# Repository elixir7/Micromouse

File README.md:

# Jerry the micromouse

# Who is Jerry?
Jerry is a tiny (10x8 cm) high performance robot for the robotics competition Micromouse. 

The competition goal is to search a 16x16 grid maze which is 3x3 m^2 as fast as possible and find the path to the center.

Then you run from start to goal with your calculated route. 

To get the competition you take 1/30 of the search time and the run time.

World class mice are extremly fast, [have a look.](https://www.youtube.com/watch?v=NqdZ9wbXt8k&t=150s)

# Structure & Development
Hardware:
-   <b>3D_Models</b>,       pcb components, motor mount, rims etc.
-   <b>drawings</b>,        .dxf files
-   <b>pcb</b>,             EAGLE CAD files
-   <b>gerbers.zip</b>,     manufacturing files for pcb (Jerry was made by [JLC PCB](https://www.jlcpcb.com)
-   <b>jlcpcb.cam</b>,      CAM job for creating gerber files to JLC standard in EAGLE.

Software:
-   <b>Eagle</b>,           E-CAD for making PCB
-   <b>Fusion 360</b>,      M-CAD for making board outline, motor mounts, rims, etc.
-   <b>Keil uVision 5</b>,  IDE for C programming/debugging on Microcontrollers

Images:
-   Renders of jerry

## Software
- MCU configuration (pins, clock, etc) using STM32CubeMX
- Keil uVision 5 project
    - Low level drivers (motors, sensors, screen)
    - High level maze solving algoritm

## Contributors
-   Isak Åslund, aslundisak@gmail.com

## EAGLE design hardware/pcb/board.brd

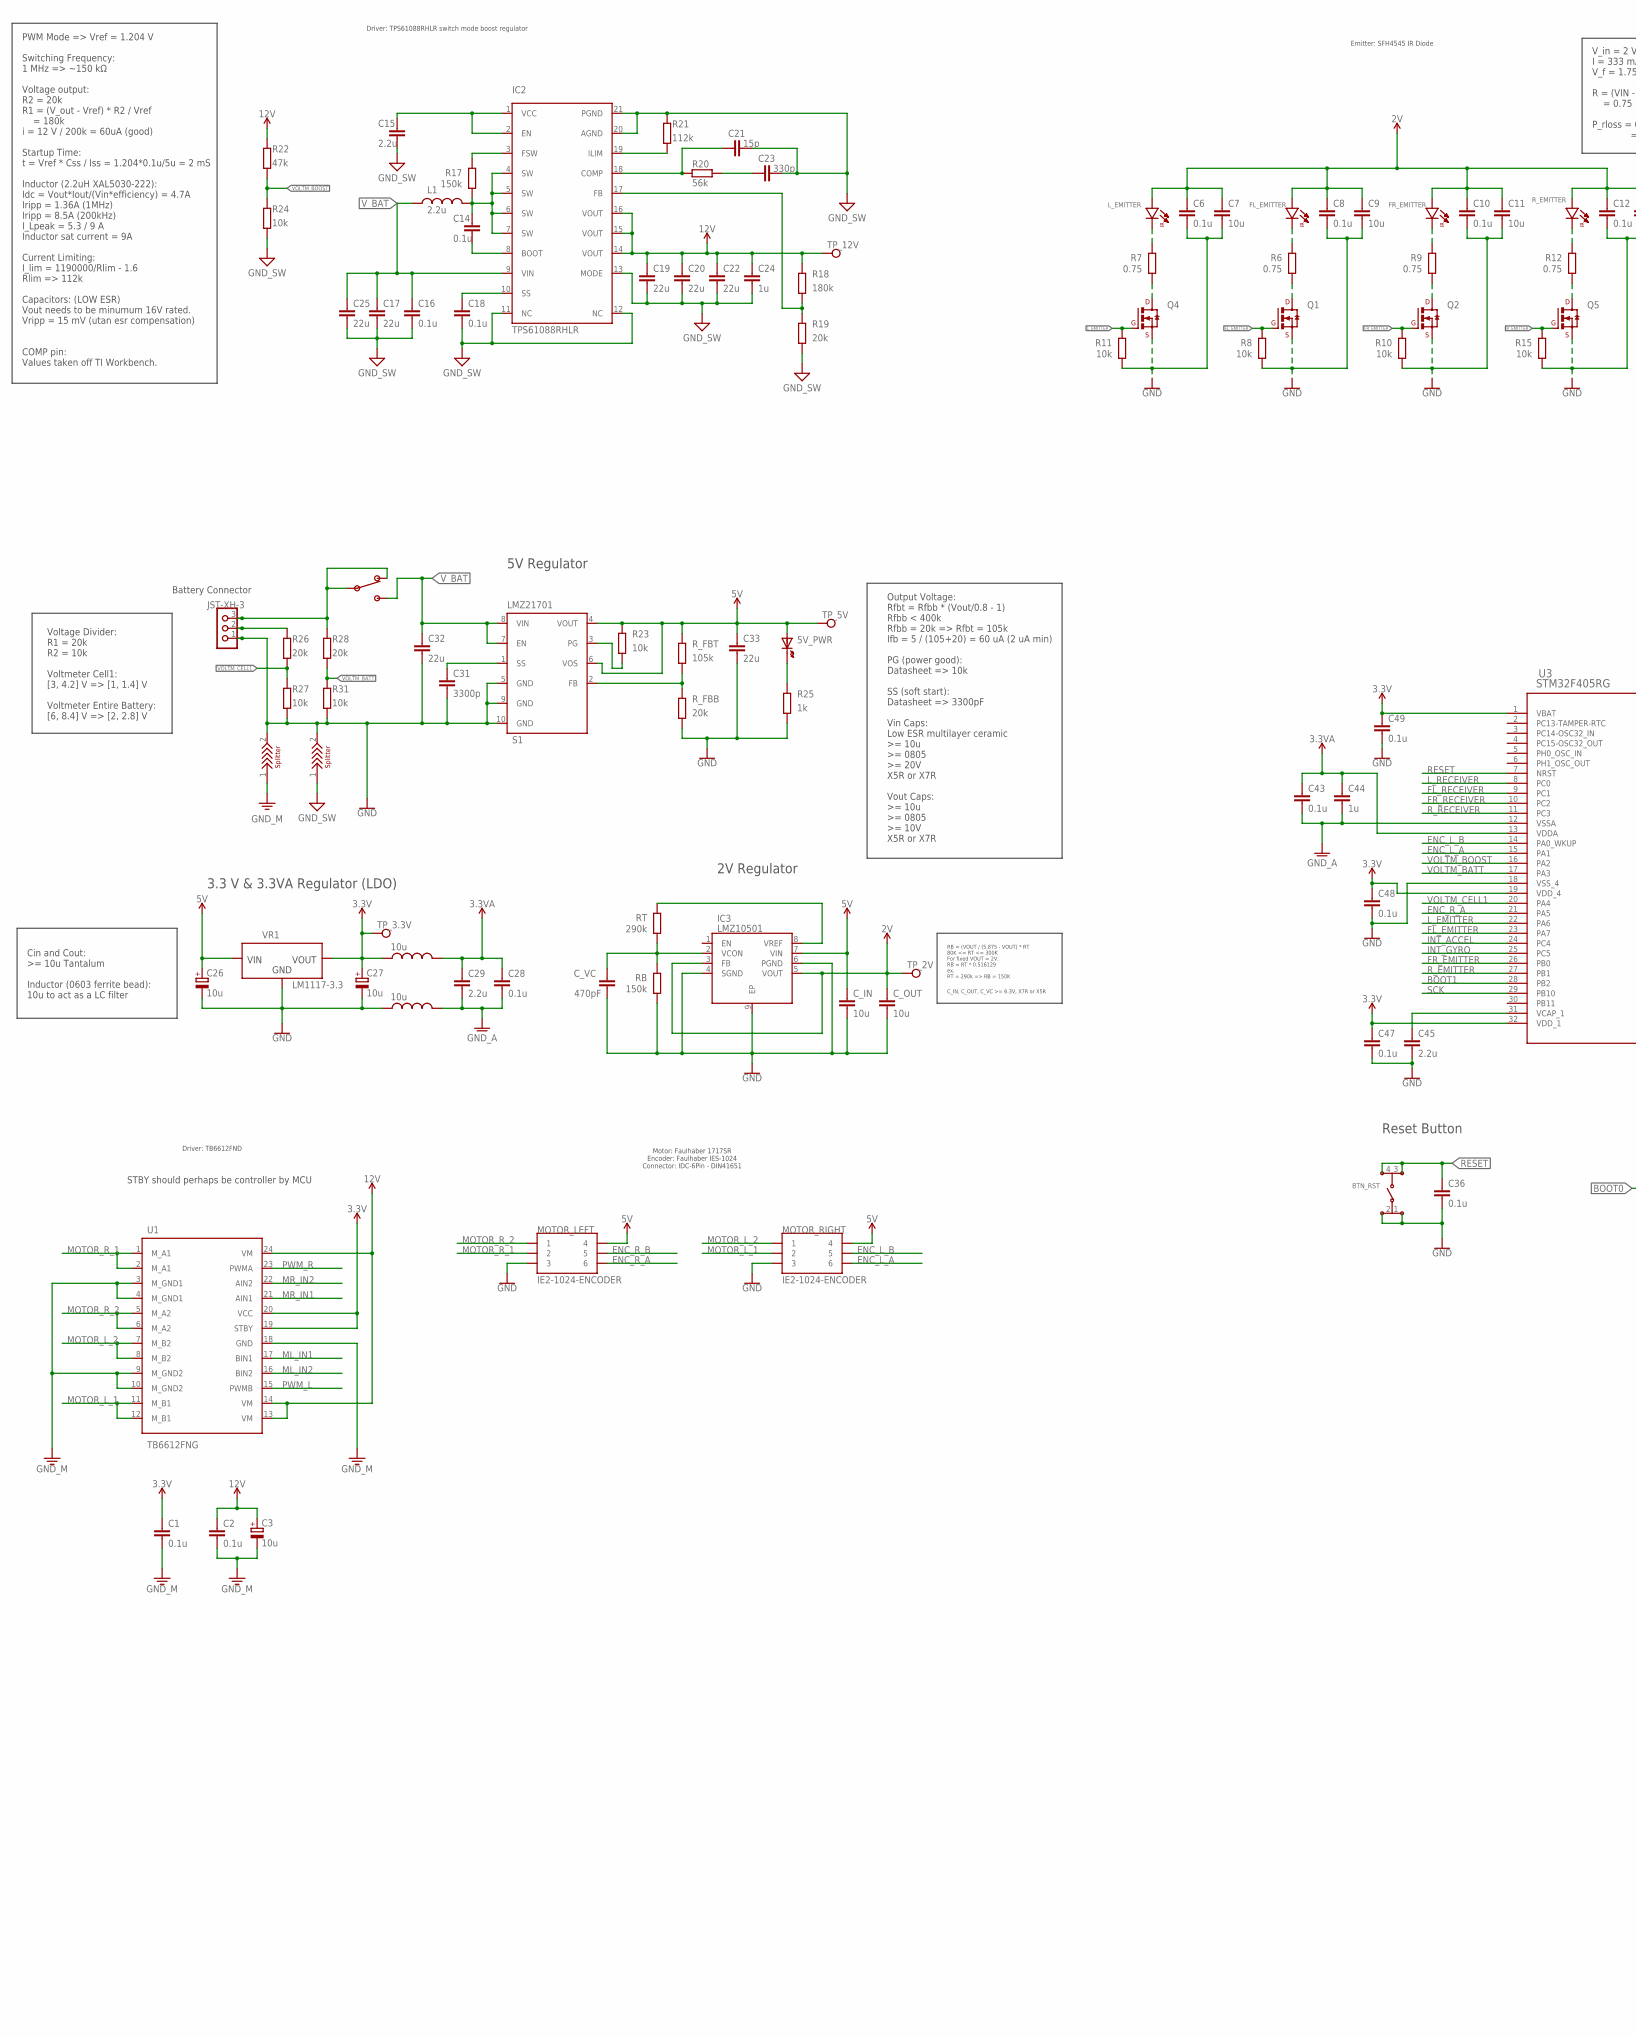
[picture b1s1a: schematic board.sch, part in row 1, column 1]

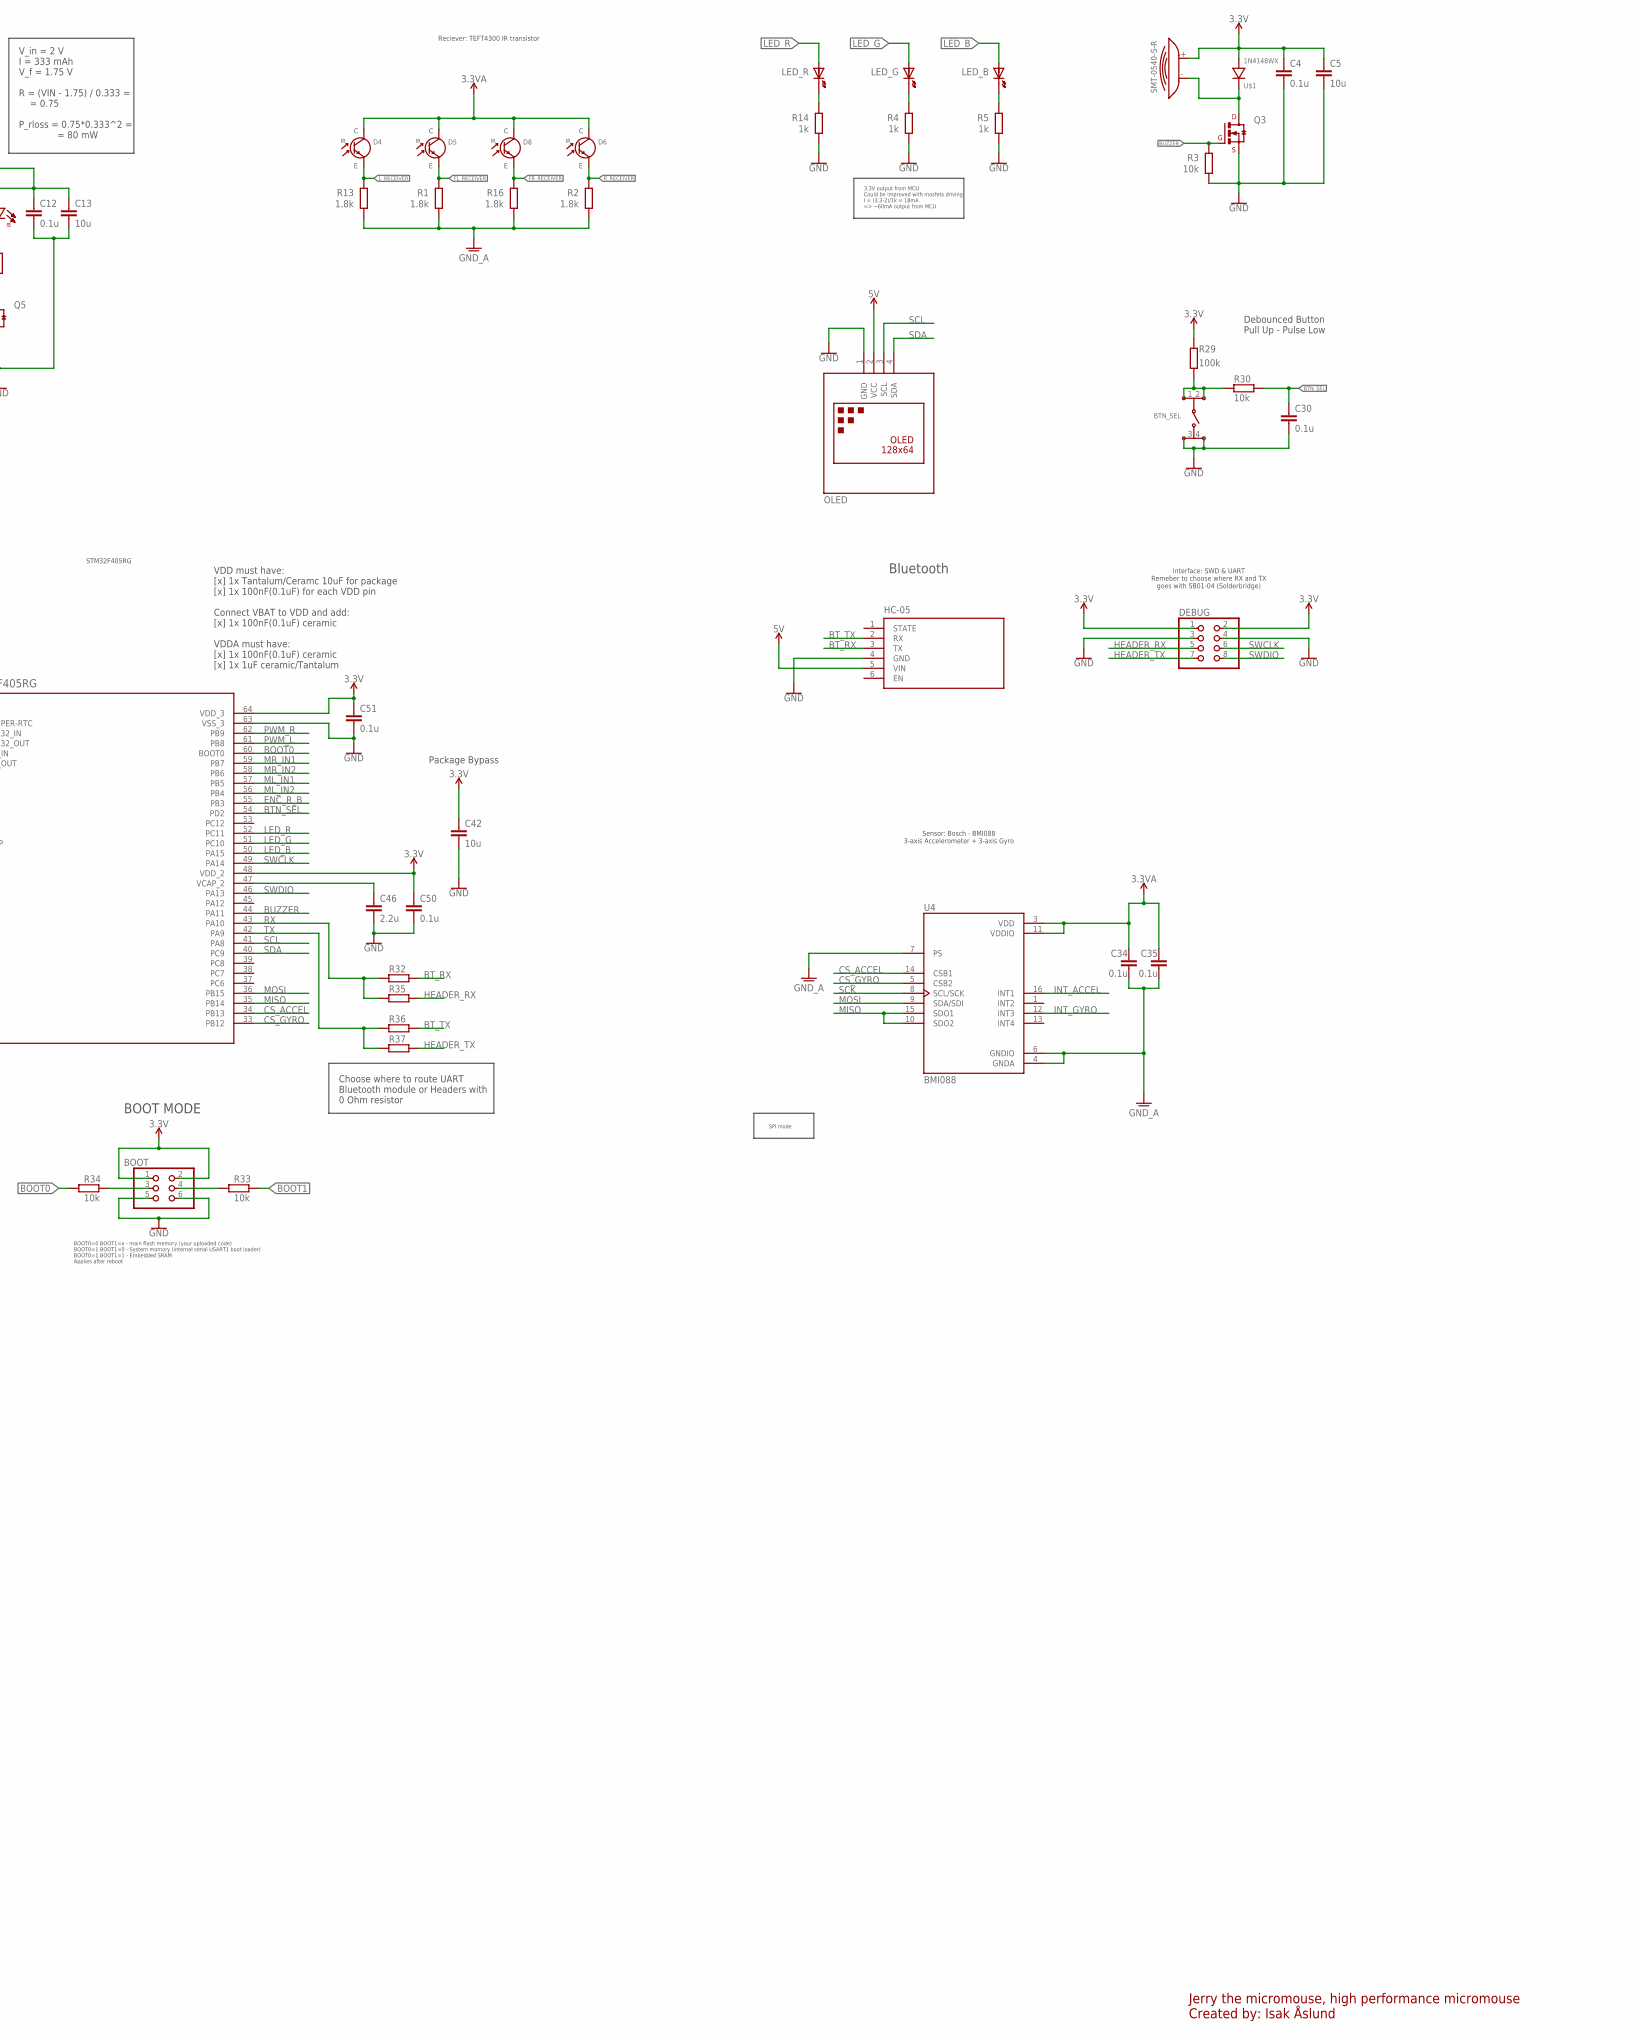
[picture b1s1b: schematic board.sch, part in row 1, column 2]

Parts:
5V_PWR: CHIP-LED0603
BOOT: PINHD-2X3; 2X03
BTN_RST: KMR621NGLFS
BTN_SEL: KMR621NGLFS
C1, C2, C4, C6, C8, C10, C12, C14, C18, C28, C30, C34, C35, C36, C43, C47, C48, C49, C50, C51: 0.1u; C0603
C3: 10u; EIA_6032-28
C5, C7, C9, C11, C13, C42: 10u; C0603
C15, C29, C45, C46: 2.2u; C0603
C16: 0.1u; C0805
C17, C19, C20, C22, C25, C33: 22u; C0805
C21: 15p; C0603
C23: 330p; C0603
C24: 1u; C0805
C26, C27: 10u; SMC_A
C31: 3300p; C0603; RATING X5R/X7R
C32: 22u; C0805; RATING X5R/X7R
C44: 1u; C0603
C_IN: 10u; C0805
C_OUT: 10u; C0805
C_VC: 470pF; C0603; RATING X5R/X7R
D4, D5, D6, D8: TEFT4300; 3MM_PHOTOTRANSISTOR
DEBUG: PINHD-2X4; 2X04
FL_EMITTER: SFH_4545
FP1, FP2: 10u; R0805
FR_EMITTER: SFH_4545
HC-05: WIRELESS-BLUETOOTH-HC-05
IC2: TPS61088RHLR; RHL(R-PVQFN-N20)_1
IC3: LMZ10501; SON65P260X300X150-9N
L1: 2.2u; XAL5030
LED_B: CHIP-LED0603
LED_G: CHIP-LED0603
LED_R: CHIP-LED0603
L_EMITTER: SFH_4545
MOTOR_LEFT: IE2-1024-ENCODER
MOTOR_RIGHT: IE2-1024-ENCODER
OLED: DISPLAY-OLED-128X64-I2C
Q1, Q2, Q3, Q4, Q5: IRFML8244TRPBF; SOT95P235X110-3
R1, R2, R13, R16: 1.8k; R0603
R3, R8, R10, R11, R15, R24, R27, R30, R31, R33, R34: 10k; R0603
R4, R5, R14, R25: 1k; R0603
R6, R7, R9, R12: 0.75; R0603
R17: 150k; R0603
R18: 180k; R0603
R19, R26, R28: 20k; R0603
R20: 56k; R0603
R21: 112k; R0603
R22: 47k; R0603
R23: 10k; R0603; TOLERANCE 1%
R29: 100k; R0603
R32, R35, R36, R37: 0; R0603
RB: 150k; R0603
RT: 290k; R0603; TOLERANCE 1%
R_EMITTER: SFH_4545
R_FBB: 20k; R0603
R_FBT: 105k; R0603
S1: LMZ21701
SW: SPDT-500SSP1S1M6QEA; 500SSP1S1M6QEA
TP_2V, TP_3.3V, TP_5V, TP_12V: TEST-POINT3X5; PAD.03X.05
U1: TB6612FNG; SOP65P760X160-24
U3: STM32F405RG; LQFP-64
U4: BMI088; PQFN50P450X300X100-16N
U$1: 1N4148WX; 1N4148WX_SOD-323-2
U$4: SMT-0540-S-R
U$6, U$7: SPLITTER
U$10: JST-XH-3; JST-XH-03
VR1: LM1117-3.3; SOT230P700X180-4

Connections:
2V: C6.1, C7.1, C8.1, C9.1, C10.1, C11.1, C12.1, C13.1, C_OUT.1, FL_EMITTER.+ (+_ANODE), FR_EMITTER.+ (+_ANODE), IC3.3 (FB), IC3.5 (VOUT), L_EMITTER.+ (+_ANODE), R_EMITTER.+ (+_ANODE), TP_2V.P$1
3.3V: BOOT.1, BOOT.2, C1.1, C4.1, C5.1, C27.+, C42.1, C47.1, C48.1, C49.1, C50.1, C51.1, DEBUG.1, DEBUG.2, FP1.1, R29.1, TP_3.3V.P$1, U1.19 (STBY), U1.20 (VCC), U3.1 (VBAT), U3.19 (VDD_4), U3.32 (VDD_1), U3.48 (VDD_2), U3.64 (VDD_3), U$1.+ (+_ANODE), U$4.+, VR1.2 (VOUT), VR1.4 (VOUT)
3.3VA: C28.1, C29.1, C34.1, C35.1, C43.1, C44.1, D4.C (C_+), D5.C (C_+), D6.C (C_+), D8.C (C_+), FP1.2, U3.13 (VDDA), U4.3 (VDD), U4.11 (VDDIO)
5V: 5V_PWR.A, C26.+, C33.1, C_IN.1, HC-05.5 (VIN), IC3.7 (VIN), MOTOR_LEFT.4, MOTOR_RIGHT.4, OLED.2 (VCC), R23.2, R_FBT.1, S1.4 (VOUT), S1.6 (VOS), TP_5V.P$1, VR1.3 (VIN)
12V: C2.1, C3.1 (+), C19.1, C20.1, C22.1, C24.1, IC2.14 (VOUT), IC2.15 (VOUT), IC2.16 (VOUT), R18.1, R22.2, TP_12V.P$1, U1.13 (VM), U1.14 (VM), U1.24 (VM)
BOOT0: R34.2, U3.60 (BOOT0)
BOOT1: R33.1, U3.28 (PB2)
BTN_SEL: C30.1, R30.2, U3.54 (PD2)
BT_RX: HC-05.3 (TX), R32.2
BT_TX: HC-05.2 (RX), R36.2
BUZZER: Q3.1 (G), R3.2, U3.44 (PA11)
CS_ACCEL: U3.34 (PB13), U4.14 (CSB1)
CS_GYRO: U3.33 (PB12), U4.5 (CSB2)
ENC_L_A: MOTOR_RIGHT.6, U3.15 (PA1)
ENC_L_B: MOTOR_RIGHT.5, U3.14 (PA0_WKUP)
ENC_R_A: MOTOR_LEFT.6, U3.21 (PA5)
ENC_R_B: MOTOR_LEFT.5, U3.55 (PB3)
FL_EMITTER: Q1.1 (G), R8.2, U3.23 (PA7)
FL_RECEIVER: D5.E (E_-), R1.2, U3.9 (PC1)
FR_EMITTER: Q2.1 (G), R10.2, U3.26 (PB0)
FR_RECEIVER: D8.E (E_-), R16.2, U3.10 (PC2)
GND: BOOT.5, BOOT.6, BTN_RST.1, BTN_RST.2, BTN_SEL.3, BTN_SEL.4, C4.2, C5.2, C6.2, C7.2, C8.2, C9.2, C10.2, C11.2, C12.2, C13.2, C26.-, C27.-, C30.2, C31.2, C32.2, C33.2, C36.2, C42.2, C45.2, C46.2, C47.2, C48.2, C49.2, C50.2, C51.2, C_IN.2, C_OUT.2, C_VC.2, DEBUG.3, DEBUG.4, FP2.1, HC-05.4 (GND), IC3.4 (SGND), IC3.6 (PGND), IC3.9 (EP), MOTOR_LEFT.3, MOTOR_RIGHT.3, OLED.1 (GND), Q1.2 (S), Q2.2 (S), Q3.2 (S), Q4.2 (S), Q5.2 (S), R3.1, R4.1, R5.1, R8.1, R10.1, R11.1, R14.1, R15.1, R25.1, R27.1, R31.1, RB.1, R_FBB.1, S1.5 (GND), S1.9 (GND), S1.10 (GND), U3.18 (VSS_4), U3.63 (VSS_3), U$6.2, U$7.2, U$10.1, VR1.1 (GND)
GND_A: C28.2, C29.2, C34.2, C35.2, C43.2, C44.2, FP2.2, R1.1, R2.1, R13.1, R16.1, U3.12 (VSSA), U4.4 (GNDA), U4.6 (GNDIO), U4.7 (PS)
GND_M: C1.2, C2.2, C3.2 (-), U1.3 (M_GND1), U1.4 (M_GND1), U1.9 (M_GND2), U1.10 (M_GND2), U1.18 (GND), U$6.1
GND_SW: C15.2, C16.2, C17.2, C18.2, C19.2, C20.2, C21.2, C22.2, C23.2, C24.2, C25.2, IC2.11 (NC), IC2.12 (NC), IC2.13 (MODE), IC2.20 (AGND), IC2.21 (PGND), R19.2, R21.2, R24.1, U$7.1
HEADER_RX: DEBUG.5, R35.2
HEADER_TX: DEBUG.7, R37.2
INT_ACCEL: U3.24 (PC4), U4.16 (INT1)
INT_GYRO: U3.25 (PC5), U4.12 (INT3)
LED_B: LED_B.A, U3.50 (PA15)
LED_G: LED_G.A, U3.51 (PC10)
LED_R: LED_R.A, U3.52 (PC11)
L_EMITTER: Q4.1 (G), R11.2, U3.22 (PA6)
L_RECEIVER: D4.E (E_-), R13.2, U3.8 (PC0)
MISO: U3.35 (PB14), U4.10 (SDO2), U4.15 (SDO1)
ML_IN1: U1.17 (BIN1), U3.57 (PB5)
ML_IN2: U1.16 (BIN2), U3.56 (PB4)
MOSI: U3.36 (PB15), U4.9 (SDA/SDI)
MOTOR_L_1: MOTOR_RIGHT.2, U1.11 (M_B1), U1.12 (M_B1)
MOTOR_L_2: MOTOR_RIGHT.1, U1.7 (M_B2), U1.8 (M_B2)
MOTOR_R_1: MOTOR_LEFT.2, U1.1 (M_A1), U1.2 (M_A1)
MOTOR_R_2: MOTOR_LEFT.1, U1.5 (M_A2), U1.6 (M_A2)
MR_IN1: U1.21 (AIN1), U3.59 (PB7)
MR_IN2: U1.22 (AIN2), U3.58 (PB6)
unnamed: Q4.3 (D), R7.1
unnamed: L_EMITTER.- (-_CATHODE), R7.2
unnamed: LED_R.C (K), R14.2
unnamed: Q1.3 (D), R6.1
unnamed: FL_EMITTER.- (-_CATHODE), R6.2
unnamed: LED_G.C (K), R4.2
unnamed: Q5.3 (D), R12.1
unnamed: Q2.3 (D), R9.1
unnamed: LED_B.C (K), R5.2
unnamed: IC3.8 (VREF), RT.2
unnamed: C_VC.1, IC3.2 (VCON), RB.2, RT.1
unnamed: R12.2, R_EMITTER.- (-_CATHODE)
unnamed: Q3.3 (D), U$1.- (-_CATHODE), U$4.-
unnamed: FR_EMITTER.- (-_CATHODE), R9.2
unnamed: C14.1, IC2.4 (SW), IC2.5 (SW), IC2.6 (SW), IC2.7 (SW), L1.2, R17.1
unnamed: IC2.3 (FSW), R17.2
unnamed: C14.2, IC2.8 (BOOT)
unnamed: C15.1, IC2.1 (VCC), IC2.2 (EN)
unnamed: C18.1, IC2.10 (SS)
unnamed: IC2.17 (FB), R18.2, R19.1
unnamed: C21.1, IC2.18 (COMP), R20.1
unnamed: IC2.19 (ILIM), R21.1
unnamed: C23.1, R20.2
unnamed: C31.1, S1.1 (SS)
unnamed: R_FBB.2, R_FBT.2, S1.2 (FB)
unnamed: R23.1, S1.3 (PG)
unnamed: 5V_PWR.C (K), R25.2
unnamed: BOOT.4, R33.2
unnamed: R26.2, U$10.2
unnamed: BOOT.3, R34.1
unnamed: BTN_SEL.1, BTN_SEL.2, R29.2, R30.1
unnamed: C45.1, U3.31 (VCAP_1)
unnamed: C46.1, U3.47 (VCAP_2)
unnamed: R28.2, SW.1, SW.2_COM (COM), U$10.3
PWM_L: U1.15 (PWMB), U3.61 (PB8)
PWM_R: U1.23 (PWMA), U3.62 (PB9)
RESET: BTN_RST.3, BTN_RST.4, C36.1, U3.7 (NRST)
RX: R32.1, R35.1, U3.43 (PA10)
R_EMITTER: Q5.1 (G), R15.2, U3.27 (PB1)
R_RECEIVER: D6.E (E_-), R2.2, U3.11 (PC3)
SCK: U3.29 (PB10), U4.8 (SCL/SCK)
SCL: OLED.3 (SCL), U3.41 (PA8)
SDA: OLED.4 (SDA), U3.40 (PC9)
SWCLK: DEBUG.6, U3.49 (PA14)
SWDIO: DEBUG.8, U3.46 (PA13)
TX: R36.1, R37.1, U3.42 (PA9)
VOLTM_BATT: R28.1, R31.2, U3.17 (PA3)
VOLTM_BOOST: R22.1, R24.2, U3.16 (PA2)
VOLTM_CELL1: R26.1, R27.2, U3.20 (PA4)
V_BAT: C16.1, C17.1, C25.1, C32.1, IC2.9 (VIN), L1.1, S1.7 (EN), S1.8 (VIN), SW.3

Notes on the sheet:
Reciever: TEFT4300 IR transistor
Emitter: SFH4545 IR Diode
Driver: TB6612FND
STM32F405RG
3.3V output from MCU Could be improved with mosfets driving I = (3.3-2)/1k = 18mA => ~60mA output from MCU
STBY should perhaps be controller by MCU
V_in = 2 V I = 333 mAh V_f = 1.75 V R = (VIN - 1.75) / 0.333 = = 0.75 P_rloss = 0.75*0.333^2 = = 80 mW
RB = (VOUT / (5.875 - VOUT) * RT 80K <= RT <= 300K For fixed VOUT = 2V: RB = RT * 0.516129 ex. RT = 290k => RB = 150K
C_IN, C_OUT, C_VC >= 6.3V, X7R or X5R
2V Regulator
PWM Mode => Vref = 1.204 V Switching Frequency: 1 MHz => ~150 kΩ Voltage output: R2 = 20k R1 = (V_out - Vref) * R2 / Vref = 180k i = 12 V / 200k = 60uA (good) Startup Time: t = Vref * Css / Iss = 1.204*0.1u/5u = 2 mS Inductor (2.2uH XAL5030-222): Idc = Vout*Iout/(Vin*efficiency) = 4.7A Iripp = 1.36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
5V Regulator
Output Voltage: Rfbt = Rfbb * (Vout/0.8 - 1) Rfbb < 400k Rfbb = 20k => Rfbt = 105k Ifb = 5 / (105+20) = 60 uA (2 uA min) PG (power good): Datasheet => 10k SS (soft start): Datasheet => 3300pF Vin Caps: Low ESR multilayer ceramic >= 10u >= 0805 >= 20V X5R or X7R Vout Caps: >= 10u >= 0805 >= 10V X5R 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
3.3 V & 3.3VA Regulator (LDO)
Cin and Cout: >= 10u Tantalum Inductor (0603 ferrite bead): 10u to act as a LC filter
Sensor: Bosch - BMI088 3-axis Accelerometer + 3-axis Gyro
Battery Connector
Voltage Divider: R1 = 20k R2 = 10k Voltmeter Cell1: [3, 4.2] V => [1, 1.4] V Voltmeter Entire Battery: [6, 8.4] V => [2, 2.8] V
SPI mode
Interface: SWD & UART Remeber to choose where RX and TX goes with SB01-04 (Solderbridge)
Motor: Faulhaber 1717SR Encoder: Faulhaber IES-1024 Connector: IDC-6Pin - DIN41651
Debounced Button Pull Up - Pulse Low
Reset Button
VDD must have: [x] 1x Tantalum/Ceramc 10uF for package [x] 1x 100nF(0.1uF) for each VDD pin Connect VBAT to VDD and add: [x] 1x 100nF(0.1uF) ceramic VDDA must have: [x] 1x 100nF(0.1uF) ceramic [x] 1x 1uF ceramic/Tantalum
Package Bypass
BOOT MODE
BOOT0=0 BOOT1=x - main flash memory (your uploaded code) BOOT0=1 BOOT1=0 - System momory (internal serial USART1 boot loader) BOOT0=1 BOOT1=1 - Embedded SRAM Applies after reboot
Bluetooth
Choose where to route UART Bluetooth module or Headers with 0 Ohm resistor
Driver: TPS61088RHLR switch mode boost regulator
Jerry the micromouse, high performance micromouse Created by: Isak Åslund

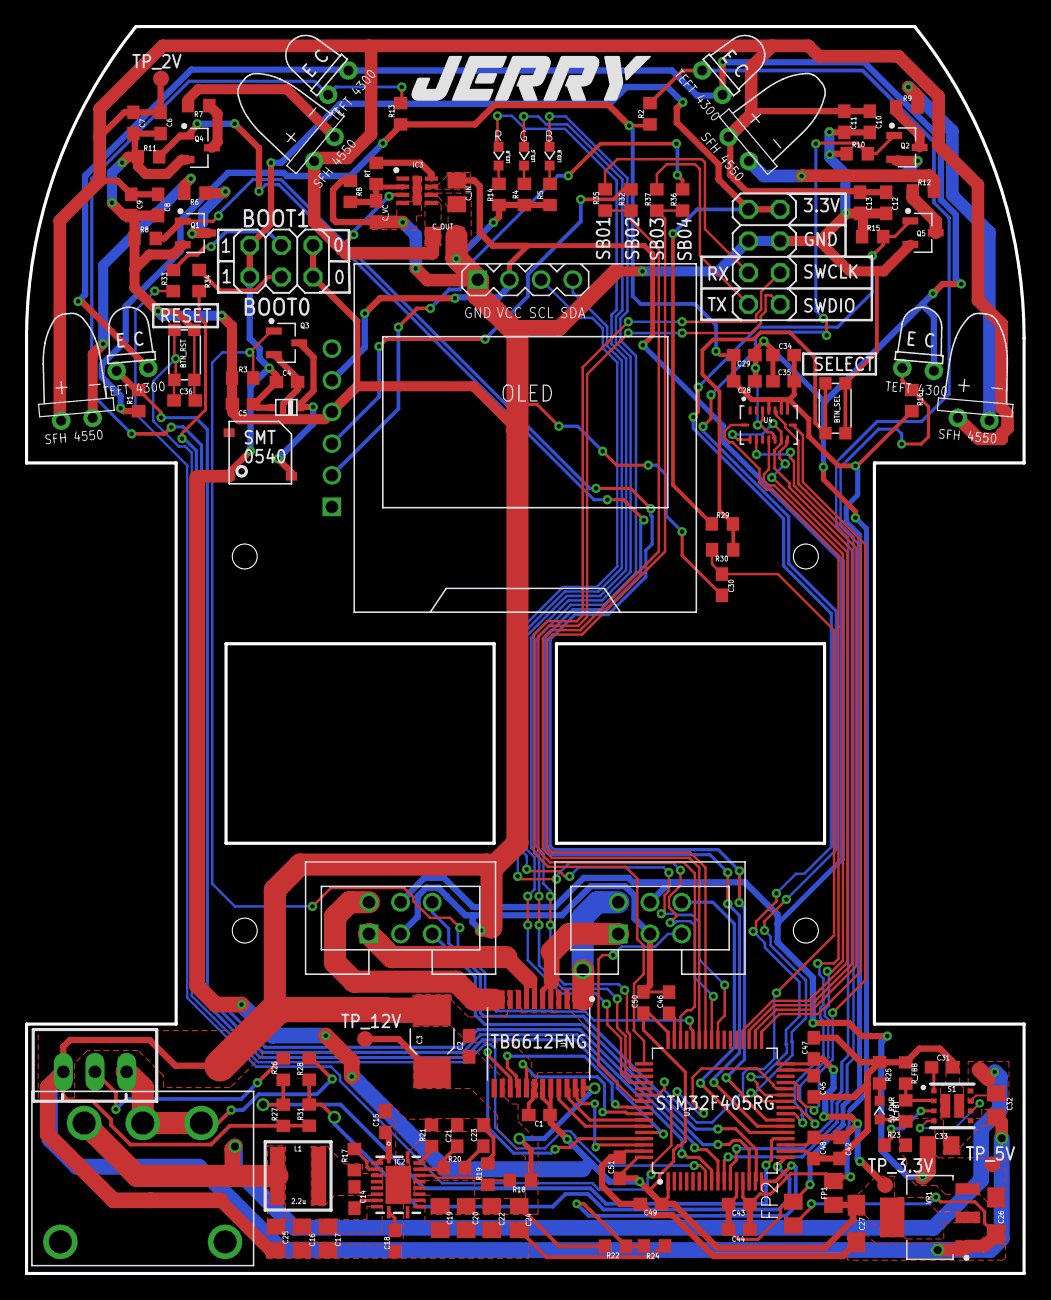
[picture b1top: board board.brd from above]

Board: 2 copper layers, 80.0 x 100.0 mm, 135 parts (1 on the bottom side), 94 nets.

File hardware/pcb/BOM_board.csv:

Cart;Qty;Value;Device;Package;Parts;TOLERANCE;V_RATING;Vendor;Link;Description
x;1;;PINHD-2X3;2X03;BOOT;;;case/crf;;PIN HEADER
x;1;;PINHD-2X4;2X04;DEBUG;;;case/crf;;PIN HEADER
x;4;0;R0603;R0603;R32, R35, R36, R37;;;mouser;;Standard Chip RESISTOR 0603 (1608 Metric)
x;20;0.1u;C0603;C0603;C1, C2, C4, C6, C8, C10, C12, C14, C18, C28, C30, C34, C35, C36, C43, C47, C48, C49, C50, C51;;;mouser;;Standard Chip CAPACITOR 0605 (1608 Metric)
x;1;0.1u;C0805;C0805;C16;;;mouser;;Standard Chip CAPACITOR 0805 (2012 Metric)
x;4;0.75;R0603;R0603;R6, R7, R9, R12;;;mouser;;Standard Chip RESISTOR 0603 (1608 Metric)
x;4;1.8k;R0603;R0603;R1, R2, R13, R16;;;mouser;;Standard Chip RESISTOR 0603 (1608 Metric)
x;1;100k;R0603;R0603;R29;;;mouser;;Standard Chip RESISTOR 0603 (1608 Metric)
x;1;105k;R0603;R0603;R_FBT;;;mouser;;Standard Chip RESISTOR 0603 (1608 Metric)
x;1;10k;R0603;R0603;R23;1%;;mouser;;Standard Chip RESISTOR 0603 (1608 Metric)
x;11;10k;R0603;R0603;R3, R8, R10, R11, R15, R24, R27, R30, R31, R33, R34;;;mouser;;Standard Chip RESISTOR 0603 (1608 Metric)
x;6;10u;C0603;C0603;C5, C7, C9, C11, C13, C42;;;mouser;;Standard Chip CAPACITOR 0605 (1608 Metric)
x;2;10u;C0805;C0805;C_IN, C_OUT;;;mouser;;Standard Chip CAPACITOR 0805 (2012 Metric)
x;1;10u;KEMET_C;EIA_6032-28;C3;;;mouser;;KEMET C Size Taltalum Capacitator
x;2;10u;SMC_A;SMC_A;C26, C27;;;mouser;;A Size Taltalum Capacitator
x;2;10u;WE-CBF_0805;R0805;FP1, FP2;;;mouser;;Würth Electronics Size 0805 Ferrite Pearls
x;1;112k;R0603;R0603;R21;;;mouser;;Standard Chip RESISTOR 0603 (1608 Metric)
x;2;150k;R0603;R0603;R17, RB;;;mouser;;Standard Chip RESISTOR 0603 (1608 Metric)
x;1;180k;R0603;R0603;R18;;;mouser;;Standard Chip RESISTOR 0603 (1608 Metric)
x;1;1N4148WX;DIODE_1N4148WX;1N4148WX_SOD-323-2;U$1;;;mouser;;
x;4;1k;R0603;R0603;R4, R5, R14, R25;;;mouser;;Standard Chip RESISTOR 0603 (1608 Metric)
x;1;1u;C0603;C0603;C44;;;mouser;;Standard Chip CAPACITOR 0605 (1608 Metric)
x;1;1u;C0805;C0805;C24;;;mouser;;Standard Chip CAPACITOR 0805 (2012 Metric)
x;4;2.2u;C0603;C0603;C15, C29, C45, C46;;;mouser;;Standard Chip CAPACITOR 0605 (1608 Metric)
x;1;2.2u;XAL5030-222MEC;XAL5030;L1;;;mouser;;COILCRAFT - XAL5030-222MEC - INDUCTOR, PWR, 2.2UH, 9.2A,20%,38MHZ
x;4;20k;R0603;R0603;R19, R26, R28, R_FBB;;;mouser;;Standard Chip RESISTOR 0603 (1608 Metric)
x;5;22u;C0805;C0805;C17, C19, C20, C22, C25;;;mouser;;Standard Chip CAPACITOR 0805 (2012 Metric)
x;1;22u;C0805;C0805;C33;;10v;mouser;;Standard Chip CAPACITOR 0805 (2012 Metric)
x;1;22u;C0805;C0805;C32;;25V;mouser;;Standard Chip CAPACITOR 0805 (2012 Metric)
x;1;27p;C0603;C0603;C21;;;mouser;;Standard Chip CAPACITOR 0605 (1608 Metric)
x;1;290k;R0603;R0603;RT;1%;;mouser;;Standard Chip RESISTOR 0603 (1608 Metric)
x;1;30k;R0603;R0603;R20;;;mouser;;Standard Chip RESISTOR 0603 (1608 Metric)
x;1;3300p;C0603;C0603;C31;;10V;mouser;;Standard Chip CAPACITOR 0605 (1608 Metric)
x;1;470pF;C0603;C0603;C_VC;;6.3V;mouser;;Standard Chip CAPACITOR 0605 (1608 Metric)
x;1;47k;R0603;R0603;R22;;;mouser;;Standard Chip RESISTOR 0603 (1608 Metric)
x;1;560p;C0603;C0603;C23;;;mouser;;Standard Chip CAPACITOR 0605 (1608 Metric)
x;1;BMI088;BMI088;PQFN50P450X300X100-16N;U4;;;mouser;;High-performance 6-axis inertial sensor (accelerometer + gyroscope)
x;4;CHIP-LED0603;CHIP-LED0603;CHIP-LED0603;5V_PWR, LED_B, LED_G, LED_R;;;mouser;;CHIP-LED0603 (SMD)
x;1;DISPLAY-OLED-128X64-I2C;DISPLAY-OLED-128X64-I2C;DISPLAY-OLED-128X64-I2C;OLED;;;mouser;;128x64 Dot Matrix OLED Module based on SSD1306 chip
x;2;IE2-1024-ENCODER;IE2-1024-ENCODER;IE2-1024-ENCODER;MOTOR_LEFT, MOTOR_RIGHT;;;mouser;;
x;5;IRFML8244TRPBF;IRFML8244TRPBF;SOT95P235X110-3;Q1, Q2, Q3, Q4, Q5;;;mouser;;IRFML8244TRPbF - N Channel Mosfet
x;1;JST-XH-3;JST-XH-3;JST-XH-03;U$10;;;mouser;;
x;2;KMR621NGLFS;KMR621NGLFS;KMR621NGLFS;BTN_RST, BTN_SEL;;;mouser;;C&K KMR621NG LFS Tactile SPST switch (SMD)
x;1;LM1117-3.3;LM1117-3.3;SOT230P700X180-4;VR1;;;mouser;;LM1117
x;1;LMZ10501;LMZ10501;SON65P260X300X150-9N;IC3;;;mouser;;Voltage Regulators - Switching Regulators 1A Nano Mod w/ 5.5V Max Inpt VTG
x;1;LMZ21701;LMZ21701;LMZ21701;S1;;;mouser;;3V to 17V, 1A Step-Down DC/DC Power Module in 3.5mm  3.5mm Package
x;4;SFH_4545;SFH_4545;SFH_4545;FL_EMITTER, FR_EMITTER, L_EMITTER, R_EMITTER;;;mouser;;High Power Infrared Emitter (940 nm)
x;1;SMT-0540-S-R;SMT-0540-S-R;SMT-0540-S-R;U$4;;;mouser;;Magnetic buzzer
x;1;SPDT-500SSP1S1M6QEA;SPDT-500SSP1S1M6QEA;500SSP1S1M6QEA;SW;;;mouser;;
NA;2;SPLITTER;SPLITTER;SPLITTER;U$6, U$7;;;NA;;Used for separating grounds
x;1;STM32F405RG;STM32F405RG;LQFP-64;U3;;;mouser;;STM32F405RG Microcontroller
x;1;TB6612FNG;TB6612FNG;SOP65P760X160-24;U1;;;mouser;;TB6612FNG - Dual DC motor driver
x;4;TEFT4300;TEFT4300;3MM_PHOTOTRANSISTOR;D4, D5, D6, D8;;;mouser;;TEFT4300 Phototransistor from Vishay
NA;4;TEST-POINT3X5;TEST-POINT3X5;PAD.03X.05;TP_2V, TP_3.3V, TP_5V, TP_12V;;;NA;;SparkFun Test Points
x;1;TPS61088RHLR;TPS61088RHLR;RHL(R-PVQFN-N20)_1;IC2;;;mouser;;DC-DC Boost Regulator
x;1;WIRELESS-BLUETOOTH-HC-05;WIRELESS-BLUETOOTH-HC-05;WIRELESS-BLUETOOTH-HC-05;HC-05;;;mouser;;Bluetooth Transceiver Module based on HC-05 board

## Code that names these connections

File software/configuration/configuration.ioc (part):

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Mcu.Name=STM32F405RGTx
Mcu.Package=LQFP64
Mcu.UserName=STM32F405RGTx
PA0-WKUP.GPIOParameters=GPIO_Label
PA0-WKUP.GPIO_Label=ENC_L_B
PA0-WKUP.Signal=S_TIM5_CH1
PA1.GPIOParameters=GPIO_Label
PA1.GPIO_Label=ENC_L_A
PA1.Signal=S_TIM5_CH2
PA10.Mode=Asynchronous
PA10.Signal=USART1_RX
PA11.GPIOParameters=GPIO_Label
PA11.GPIO_Label=BUZZER
PA11.Signal=S_TIM1_CH4
PA13.GPIOParameters=GPIO_Label
PA13.GPIO_Label=SWDIO
PA13.Mode=Serial_Wire
PA13.Signal=SYS_JTMS-SWDIO
PA14.GPIOParameters=GPIO_Label
PA14.GPIO_Label=SWCLK
PA14.Mode=Serial_Wire
PA14.Signal=SYS_JTCK-SWCLK
PA15.GPIOParameters=GPIO_Label
PA15.GPIO_Label=LED_B
PA15.Signal=GPIO_Output
PA2.GPIOParameters=GPIO_Label
PA2.GPIO_Label=VOLTM_BOOST
PA2.Signal=ADCx_IN2
PA3.GPIOParameters=GPIO_Label
PA3.GPIO_Label=VOLTM_BATT
PA3.Signal=ADCx_IN3
PA4.GPIOParameters=GPIO_Label
PA4.GPIO_Label=VOLTM_CELL1
PA4.Signal=ADCx_IN4
PA5.GPIOParameters=GPIO_Label
PA5.GPIO_Label=ENC_R_A
PA5.Signal=S_TIM2_CH1_ETR
PA6.GPIOParameters=GPIO_Label
PA6.GPIO_Label=L_EMITTER
PA6.Signal=S_TIM3_CH1
PA7.GPIOParameters=GPIO_Label
PA7.GPIO_Label=FL_EMITTER
PA7.Signal=S_TIM3_CH2
PA8.Mode=I2C
PA8.Signal=I2C3_SCL
PA9.Mode=Asynchronous
PA9.Signal=USART1_TX
PB0.GPIOParameters=GPIO_Label
PB0.GPIO_Label=FR_EMITTER
PB0.Signal=S_TIM3_CH3
PB1.GPIOParameters=GPIO_Label
PB1.GPIO_Label=R_EMITTER
PB1.Signal=S_TIM3_CH4
PB10.GPIOParameters=GPIO_Label
PB10.GPIO_Label=SCK
PB10.Mode=Full_Duplex_Master
PB10.Signal=SPI2_SCK
PB12.GPIOParameters=GPIO_Label
PB12.GPIO_Label=CS_GYRO
PB12.Signal=GPIO_Output
PB13.GPIOParameters=GPIO_Label
PB13.GPIO_Label=CS_ACCEL
PB13.Signal=GPIO_Output
PB14.GPIOParameters=GPIO_Label
PB14.GPIO_Label=MISO
PB14.Mode=Full_Duplex_Master
PB14.Signal=SPI2_MISO
PB15.GPIOParameters=GPIO_Label
PB15.GPIO_Label=MOSI
PB15.Mode=Full_Duplex_Master
PB15.Signal=SPI2_MOSI
PB2.GPIOParameters=GPIO_Label
PB2.GPIO_Label=BOOT1
PB2.Signal=GPIO_Input
PB3.GPIOParameters=GPIO_Label
PB3.GPIO_Label=ENC_R_B
PB3.Signal=S_TIM2_CH2
PB4.GPIOParameters=GPIO_Label
PB4.GPIO_Label=MOTOR_L_IN2
PB4.Signal=GPIO_Output
PB5.GPIOParameters=GPIO_Label
PB5.GPIO_Label=MOTOR_L_IN1
PB5.Signal=GPIO_Output
PB6.GPIOParameters=GPIO_Label
PB6.GPIO_Label=MOTOR_R_IN2
PB6.Signal=GPIO_Output
PB7.GPIOParameters=GPIO_Label
PB7.GPIO_Label=MOTOR_R_IN1
PB7.Signal=GPIO_Output
PB8.GPIOParameters=GPIO_Label
PB8.GPIO_Label=MOTOR_PWM_L
PB8.Signal=S_TIM4_CH3
PB9.GPIOParameters=GPIO_Label
PB9.GPIO_Label=MOTOR_PWM_R
PB9.Signal=S_TIM4_CH4
PC0.GPIOParameters=GPIO_Label
PC0.GPIO_Label=L_RECEIVER
PC0.Signal=ADCx_IN10
PC1.GPIOParameters=GPIO_Label
PC1.GPIO_Label=FL_RECEIVER
PC1.Signal=ADCx_IN11
PC10.GPIOParameters=GPIO_Label
PC10.GPIO_Label=LED_G
PC10.Signal=GPIO_Output
PC11.GPIOParameters=GPIO_Label
PC11.GPIO_Label=LED_R
PC11.Signal=GPIO_Output
PC2.GPIOParameters=GPIO_Label
PC2.GPIO_Label=FR_RECEIVER
PC2.Signal=ADCx_IN12
PC3.GPIOParameters=GPIO_Label
PC3.GPIO_Label=R_RECEIVER
PC3.Signal=ADCx_IN13
PC4.GPIOParameters=GPIO_Label
PC4.GPIO_Label=INT_ACCEL
PC4.Signal=GPXTI4
PC5.GPIOParameters=GPIO_Label
PC5.GPIO_Label=INT_GYRO
PC5.Signal=GPXTI5
PC9.Mode=I2C
PC9.Signal=I2C3_SDA
PD2.GPIOParameters=GPIO_Label
PD2.GPIO_Label=BUTTON_SELECT
PD2.Signal=GPXTI2
PH0-OSC_IN.Mode=HSE-External-Oscillator
PH0-OSC_IN.Signal=RCC_OSC_IN
PH1-OSC_OUT.Mode=HSE-External-Oscillator
PH1-OSC_OUT.Signal=RCC_OSC_OUT
RCC.HSE_VALUE=25000000
RCC.SYSCLKFreq_VALUE=16000000
board=custom

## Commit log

2019-06-06 Initial Upload
    Just some basic components added with symbols, footprints and 3D packages.
2019-07-07 Update Motor driver -> MAX14870
2019-08-01 2V regulator + new motor driver
    Changed motor driver from MAX14870 to TB6612FNG for easier soldering. Added a 2V switching DC regulator for more efficient emitter driving.
2019-08-07 Power Regulators + Created board file
    Alot has been done in this update.
2019-08-12 Voltmeter Monitors on Boost, Batt, Cell1 and 5V Power LED
2019-08-12 Visual update for ground splitter
2019-08-24 Software Folder + cubemx
2019-08-24 Changed IMU to bosch BMI088
2019-08-26 Pin Setup on MCU
2019-08-26 VSS + VDD
2019-08-29 Oled + Hc05
2019-08-29 gitignore
2019-08-29 Regulator board placement
2019-08-29 switch layout on board
2019-08-31 Eagle 9.5 persistent group update
2019-09-01 3D Packages update
2019-09-01 More 3D Models
2019-09-02 3D packages and footprint updates + board picture
2019-09-03 3D packages + component layout
2019-09-05 Routing power
2019-09-06 Routing top side
2019-09-07 Folder structure update and routing on PCB
2019-09-09 silcscreen changes
2019-09-10 TPS61088 update
2019-09-10 small tps update
2019-09-23 Exports
2019-09-24 BOM update
2019-10-04 Removed backup files
    Eagle generated backup files, removed those
2019-10-13 Keil Setup
2019-10-13 Bug fix on project setup
2019-10-14 Battery ADC DMA printout
2019-10-14 Motor Test
2019-10-14 Button interrupt
2019-10-15 Battery Voltage Sampling
2019-10-17 Battery & Motor API
2019-10-17 oled error print function
2019-10-17 frequency change on motor PWM + error printing
2019-10-17 OLED MENU init
2019-10-17 button select menu
2019-11-23 bitmap drawer (almost working)
2019-11-23 bitmap drawer (implemented) + start on new screen algo
2019-11-24 Cursor improvement
2019-11-24 Bluetooth implementation + cat bitmap
2020-02-05 Ignore compiled files
2020-02-05 Keil update

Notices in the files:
parts and their libraries:
SparkFun-PowerSymbols: Licensing: Creative Commons ShareAlike 4.0 International - https://creativecommons.org/licenses/by-sa/4.0
